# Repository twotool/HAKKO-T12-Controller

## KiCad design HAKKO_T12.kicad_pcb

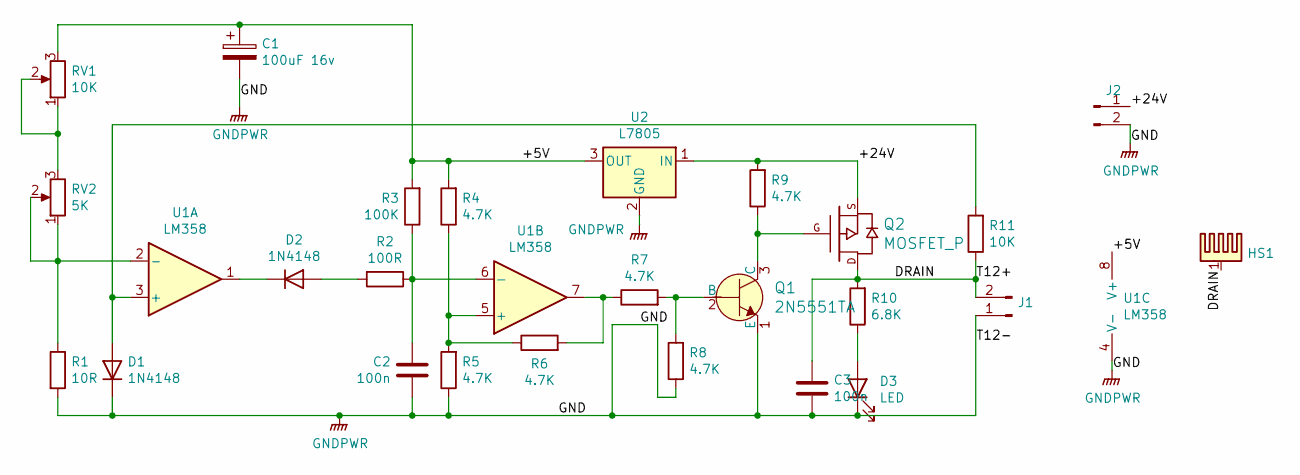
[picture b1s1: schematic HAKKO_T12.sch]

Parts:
C1: 100uF 16v; CP_Radial_D8.0mm_P3.80mm
C2, C3: 100n; C_Disc_D5.0mm_W2.5mm_P5.00mm
D1, D2: 1N4148; D_DO-41_SOD81_P10.16mm_Horizontal
D3: LED; LED_D5.0mm
HS1: Heatsink_Pad; Heatsink_14x9mm_1xDrill1.5mm
J1, J2: Conn_01x02_Male; LINE CN
Q1: 2N5551TA; TO-92-3_Formed_Leads; MPN 2N5551TA; Digi-Key_PN 2N5551TAFSCT-ND
Q2: MOSFET_P; TO-220-3_Vertical_P_Channel_MOSFET
R1: 10R; R_Axial_DIN0207_L6.3mm_D2.5mm_P10.16mm_Horizontal
R2: 100R; R_Axial_DIN0207_L6.3mm_D2.5mm_P10.16mm_Horizontal
R3: 100K; R_Axial_DIN0207_L6.3mm_D2.5mm_P10.16mm_Horizontal
R4, R5, R6, R7, R8, R9: 4.7K; R_Axial_DIN0207_L6.3mm_D2.5mm_P10.16mm_Horizontal
R10: 6.8K; R_Axial_DIN0207_L6.3mm_D2.5mm_P10.16mm_Horizontal
R11: 10K; R_Axial_DIN0207_L6.3mm_D2.5mm_P10.16mm_Horizontal
RV1: 10K; Potentiometer_Bourns_3386C_Horizontal
RV2: 5K; Big_POT
U1: LM358; DIP-8_W7.62mm_Socket_LongPads
U2: L7805; TO-220-3_Vertical

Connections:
/+5V: C1.1, R3.2, R4.2, RV1.3, U1.8 (V+), U2.3 (OUT)
/+24V: J2.1, Q2.S, R9.2, U2.1 (IN)
/DRAIN: C3.1, HS1.1, J1.2, Q2.D, R10.2, R11.1
GNDPWR: C1.2, C2.2, C3.2, D1.1 (K), D3.1 (K), J1.1, J2.2, Q1.1 (E), R1.2, R5.1, R8.1, U1.4 (V-), U2.2 (GND)
unnamed: C2.1, R2.1, R3.1, U1.6 (-)
unnamed: D1.2 (A), R11.2, U1.3 (+)
unnamed: D2.1 (K), U1.1
unnamed: D2.2 (A), R2.2
unnamed: D3.2 (A), R10.1
unnamed: Q1.2 (B), R7.2, R8.2
unnamed: Q1.3 (C), Q2.G, R9.1
unnamed: R1.1, RV2.1, RV2.2, U1.2 (-)
unnamed: R4.1, R5.2, R6.1, U1.5 (+)
unnamed: R6.2, R7.1, U1.7
unnamed: RV1.1, RV1.2, RV2.3

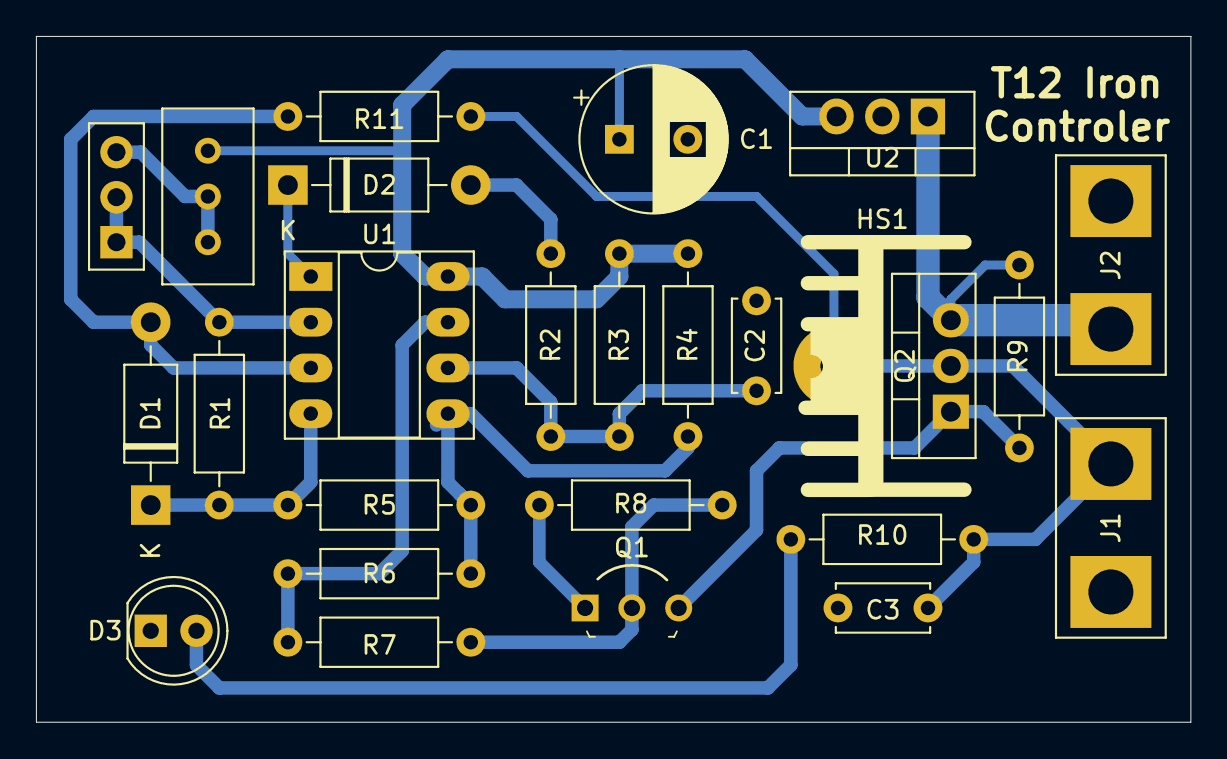
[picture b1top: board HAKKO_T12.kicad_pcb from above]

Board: 2 copper layers, 64.1 x 38.1 mm, 26 parts (0 on the bottom side), 15 nets.

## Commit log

2022-07-24 Fist commit
